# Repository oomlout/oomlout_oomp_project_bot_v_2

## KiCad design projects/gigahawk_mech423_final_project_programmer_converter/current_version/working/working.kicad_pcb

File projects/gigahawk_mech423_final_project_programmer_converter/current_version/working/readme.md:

# mech423_final_project
 
## summary 
* id: gigahawk_mech423_final_project_programmer_converter
* user: gigahawk
* name: mech423_final_project
* board: programmer_converter
* repo: https://github.com/Gigahawk/mech423_final_project
* src_file_repo_kicad_pcb: pcb/logic_handle.kicad_pcb
* src_file_repo_kicad_pcb_link: https://github.com/Gigahawk/mech423_final_project/tree/master/pcb/logic_handle.kicad_pcb
* src_file_repo_kicad_sch: pcb/conn_common.kicad_sch
* src_file_repo_kicad_sch_link: https://github.com/Gigahawk/mech423_final_project/tree/master/pcb/conn_common.kicad_sch

* src_file_repo_sch: 
* src_file_repo_sch_link: https://github.com/Gigahawk/mech423_final_project/tree/master/
* full details link: https://github.com/oomlout/oomlout_oomp_project_bot_v_2/tree/main/projects/gigahawk_mech423_final_project_programmer_converter/current_version/working

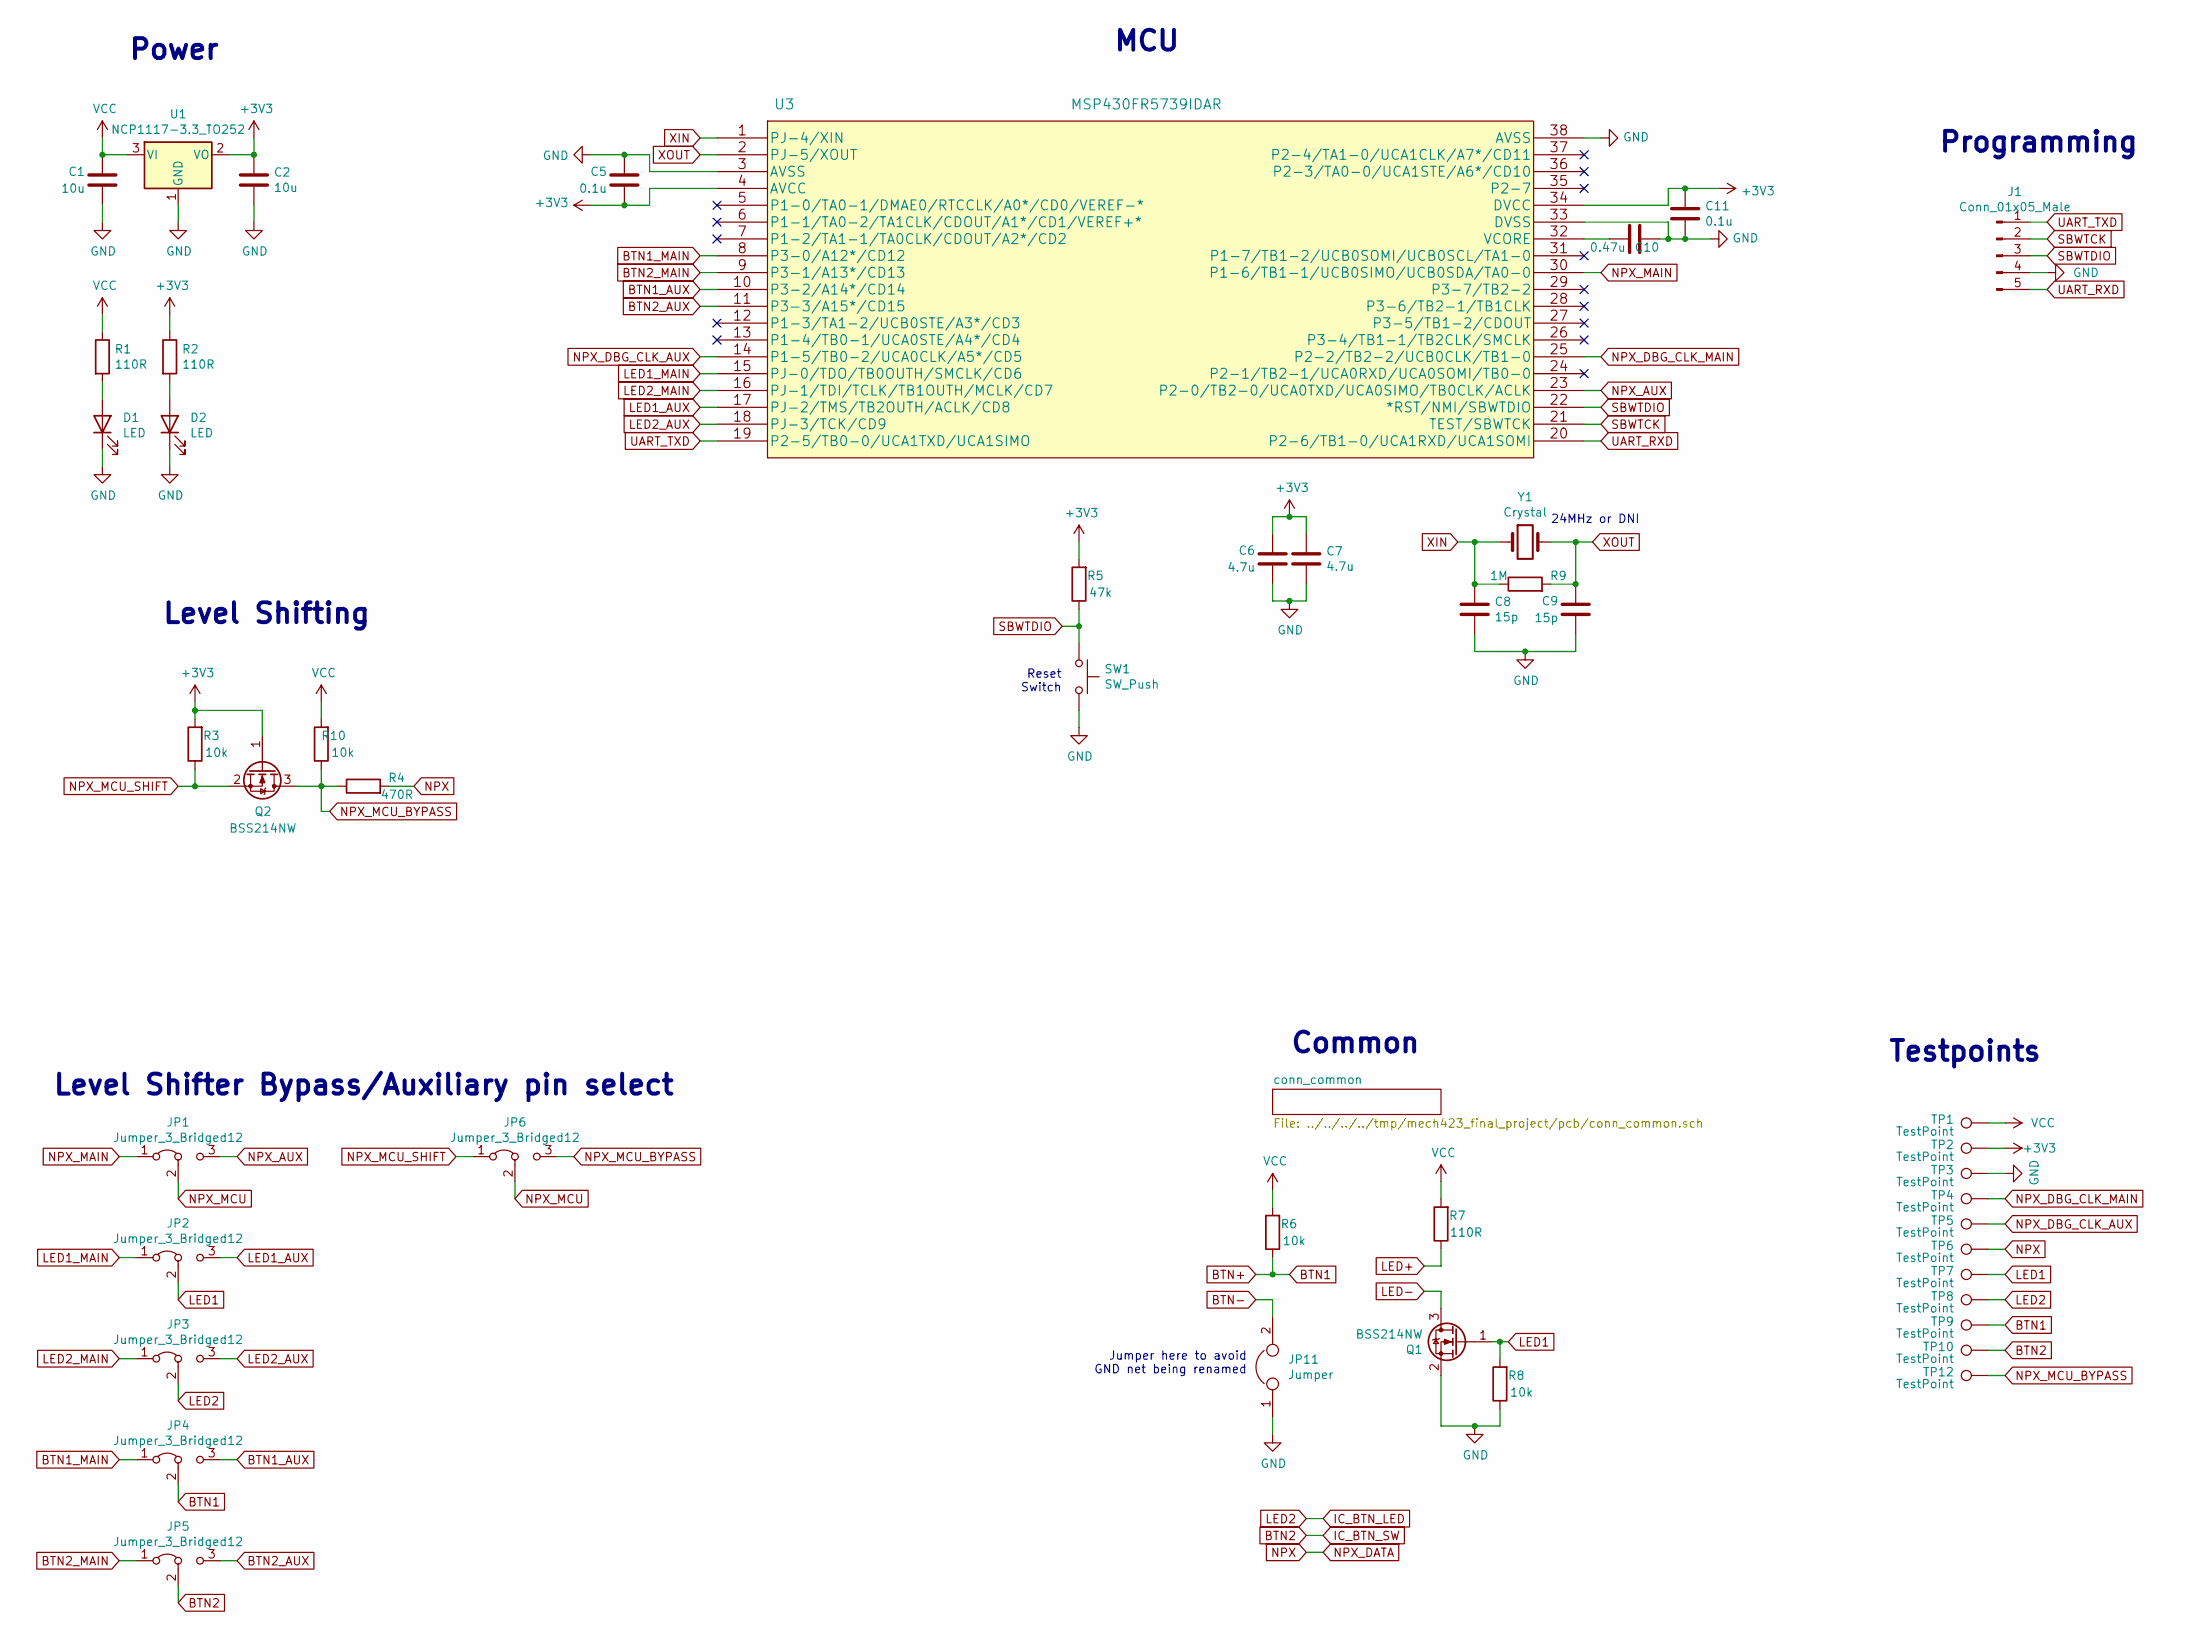
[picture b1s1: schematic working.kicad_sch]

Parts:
C1, C2: 10u; C_0805_2012Metric; Digikey 1276-6456-1-ND
C5, C11: 0.1u; C_0805_2012Metric; Digikey 478-10836-1-ND
C6, C7: 4.7u; C_0805_2012Metric; Digikey 1276-1259-1-ND
C8, C9: 15p; C_0805_2012Metric; Digikey 478-1306-1-ND
C10: 0.47u; C_0805_2012Metric; Digikey 478-10438-1-ND
D1, D2: LED; LED_0603_1608Metric; Digikey 160-1832-1-ND
J1: Conn_01x05_Male; PinHeader_1x05_P2.54mm_Vertical
JP1, JP2, JP3, JP4, JP5, JP6: Jumper_3_Bridged12; SolderJumper-3_P1.3mm_Bridged2Bar12_Pad1.0x1.5mm
JP11: Jumper; SolderJumper-2_P1.3mm_Bridged2Bar_Pad1.0x1.5mm
Q1, Q2: BSS214NW; SOT-323_SC-70; Digikey BSS214NWH6327XTSA1CT-ND
R1, R2, R7: 110R; R_0805_2012Metric; Digikey RMCF0805JT110RCT-ND
R3, R6, R8, R10: 10k; R_0805_2012Metric; Digikey RMCF0805JT10K0CT-ND
R4: 470R; R_0805_2012Metric; Digikey A129745CT-ND
R5: 47k; R_0805_2012Metric; Digikey A130144CT-ND
R9: 1M; R_0805_2012Metric; Digikey A106058CT-ND
SW1: SW_Push; SW_SPST_TL3342; Digikey EG5470CT-ND
TP1, TP2, TP3, TP4, TP5, TP6, TP7, TP8, TP9, TP10, TP12: TestPoint; TestPoint_Pad_2.0x2.0mm
U1: NCP1117-3.3_TO252; TO-252-2; Digikey NCP1117ST33T3GOSCT-ND
U3: MSP430FR5739IDAR; Digikey 296-29235-1-ND
Y1: Crystal; Crystal_SMD_AWSZT-CV-2Pin_3.7x3.1mm; Digikey 535-10028-2-ND

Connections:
+3V3: C2.1, C5.1, C6.2, C7.1, C11.1, Q2.1 (G), R2.1, R3.2, R5.2, TP2.1, U1.2 (VO), U3.4 (AVCC), U3.34 (DVCC)
BTN1_AUX: JP4.3 (B), U3.10 (P3-2/A14*/CD14)
BTN1_MAIN: JP4.1 (A), U3.8 (P3-0/A12*/CD12)
BTN2: JP5.2 (C), TP10.1; also elsewhere on the board
BTN2_AUX: JP5.3 (B), U3.11 (P3-3/A15*/CD15)
BTN2_MAIN: JP5.1 (A), U3.9 (P3-1/A13*/CD13)
BTN+: JP4.2 (C), R6.1, TP9.1; also elsewhere on the board
BTN-: JP11.2; also elsewhere on the board
GND: C1.1, C2.2, C5.2, C6.1, C7.2, C8.2, C9.1, C10.2, C11.2, D1.1 (K), D2.1 (K), J1.4, JP11.1, Q1.2 (S), R8.1, SW1.2, TP3.1, U1.1 (GND), U3.3 (AVSS), U3.33 (DVSS), U3.38 (AVSS); also elsewhere on the board
IC_BTN_LED: JP3.2 (C), TP8.1; also elsewhere on the board
LED1: JP2.2 (C), Q1.1 (G), R8.2, TP7.1
LED1_AUX: JP2.3 (B), U3.17 (PJ-2/TMS/TB2OUTH/ACLK/CD8)
LED1_MAIN: JP2.1 (A), U3.15 (PJ-0/TDO/TB0OUTH/SMCLK/CD6)
LED2_AUX: JP3.3 (B), U3.18 (PJ-3/TCK/CD9)
LED2_MAIN: JP3.1 (A), U3.16 (PJ-1/TDI/TCLK/TB1OUTH/MCLK/CD7)
LED+: R7.1; also elsewhere on the board
LED-: Q1.3 (D); also elsewhere on the board
NPX: R4.2, TP6.1; also elsewhere on the board
NPX_AUX: JP1.3 (B), U3.23 (P2-0/TB2-0/UCA0TXD/UCA0SIMO/TB0CLK/ACLK)
NPX_DBG_CLK_AUX: TP5.1, U3.14 (P1-5/TB0-2/UCA0CLK/A5*/CD5)
NPX_DBG_CLK_MAIN: TP4.1, U3.25 (P2-2/TB2-2/UCB0CLK/TB1-0)
NPX_MAIN: JP1.1 (A), U3.30 (P1-6/TB1-1/UCB0SIMO/UCB0SDA/TA0-0)
NPX_MCU: JP1.2 (C), JP6.2 (C)
NPX_MCU_BYPASS: JP6.3 (B), Q2.3 (D), R4.1, R10.1, TP12.1
NPX_MCU_SHIFT: JP6.1 (A), Q2.2 (S), R3.1
unnamed: C10.1, U3.32 (VCORE)
unnamed: D1.2 (A), R1.2
unnamed: D2.2 (A), R2.2
SBWTCK: J1.2, U3.21 (TEST/SBWTCK)
SBWTDIO: J1.3, R5.1, SW1.1, U3.22 (*RST/NMI/SBWTDIO)
UART_RXD: J1.5, U3.20 (P2-6/TB1-0/UCA1RXD/UCA1SOMI)
UART_TXD: J1.1, U3.19 (P2-5/TB0-0/UCA1TXD/UCA1SIMO)
VCC: C1.2, R1.1, R6.2, R7.2, R10.2, TP1.1, U1.3 (VI); also elsewhere on the board
XIN: C8.1, R9.1, U3.1 (PJ-4/XIN), Y1.1
XOUT: C9.2, R9.2, U3.2 (PJ-5/XOUT), Y1.2

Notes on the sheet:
Programming
Level Shifting
Level Shifter Bypass/Auxiliary pin select
Jumper here to avoid GND net being renamed
Testpoints
Reset Switch
24MHz or DNI
Power
Common
MCU

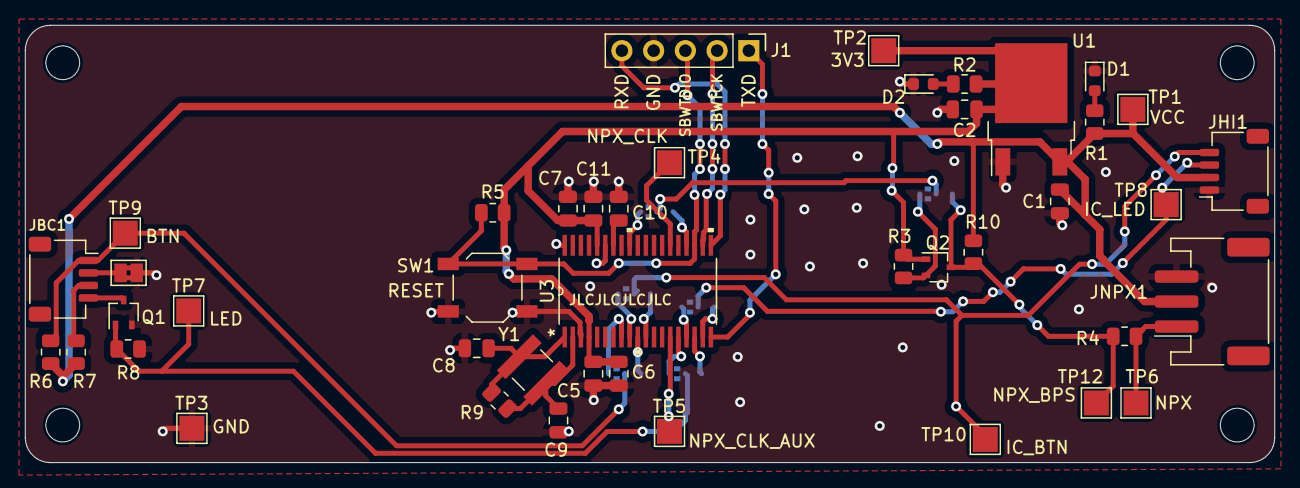
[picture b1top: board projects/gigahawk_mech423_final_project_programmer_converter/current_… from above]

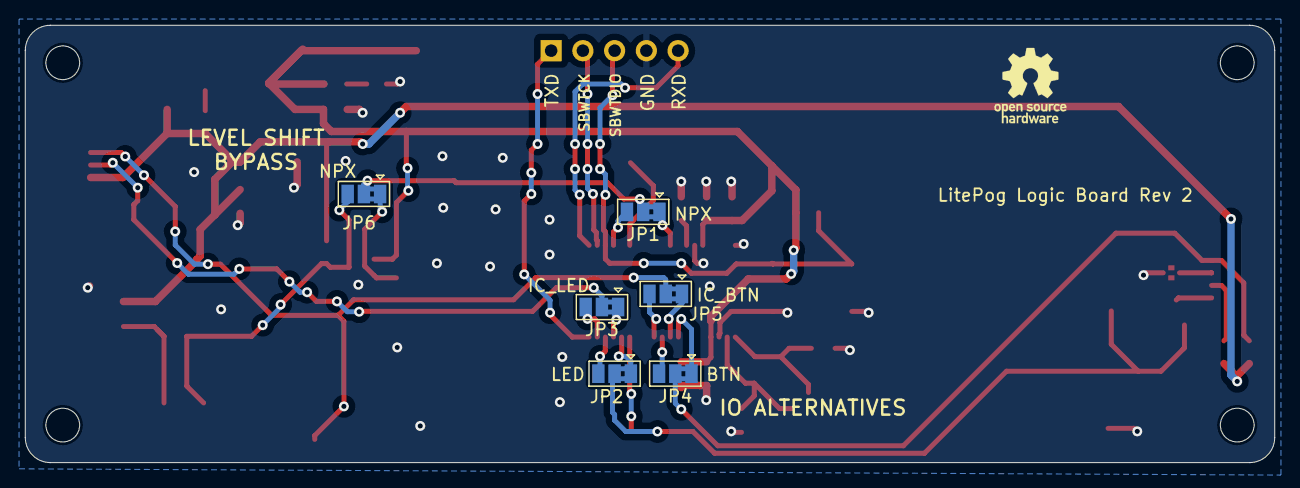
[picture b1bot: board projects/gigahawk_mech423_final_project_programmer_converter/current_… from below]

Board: 2 copper layers, 100.0 x 35.0 mm, 54 parts (7 on the bottom side), 35 nets.

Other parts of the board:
H1, H2, H3, H4: MountingHole; MountingHole_2.7mm_M2.5
JBC1: Conn_01x04; JST_SH_SM04B-SRSS-TB_1x04-1MP_P1.00mm_Horizontal
JHI1: Conn_01x04; JST_SH_SM04B-SRSS-TB_1x04-1MP_P1.00mm_Horizontal
JNPX1: Conn_01x03; JST_PH_S3B-PH-SM4-TB_1x03-1MP_P2.00mm_Horizontal
LOGO1: Logo_Open_Hardware_Small; OSHW-Logo_5.7x6mm_SilkScreen

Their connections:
BTN2: JHI1.4; also elsewhere on the board
BTN+: JBC1.1; also elsewhere on the board
BTN-: JBC1.2; also elsewhere on the board
GND: JHI1.1, JNPX1.3; also elsewhere on the board
IC_BTN_LED: JHI1.3; also elsewhere on the board
LED+: JBC1.3; also elsewhere on the board
LED-: JBC1.4; also elsewhere on the board
NPX: JNPX1.1; also elsewhere on the board
VCC: JHI1.2, JNPX1.2; also elsewhere on the board

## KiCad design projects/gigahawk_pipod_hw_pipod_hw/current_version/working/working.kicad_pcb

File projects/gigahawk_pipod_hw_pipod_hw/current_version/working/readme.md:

# pipod_hw
 
## summary 
* id: gigahawk_pipod_hw_pipod_hw
* user: gigahawk
* name: pipod_hw
* board: pipod_hw
* repo: https://github.com/Gigahawk/pipod_hw
* src_file_repo_kicad_pcb: pipod_compute.kicad_pcb
* src_file_repo_kicad_pcb_link: https://github.com/Gigahawk/pipod_hw/tree/master/pipod_compute.kicad_pcb
* src_file_repo_kicad_sch: audio.kicad_sch
* src_file_repo_kicad_sch_link: https://github.com/Gigahawk/pipod_hw/tree/master/audio.kicad_sch

* src_file_repo_sch: 
* src_file_repo_sch_link: https://github.com/Gigahawk/pipod_hw/tree/master/
* full details link: https://github.com/oomlout/oomlout_oomp_project_bot_v_2/tree/main/projects/gigahawk_pipod_hw_pipod_hw/current_version/working

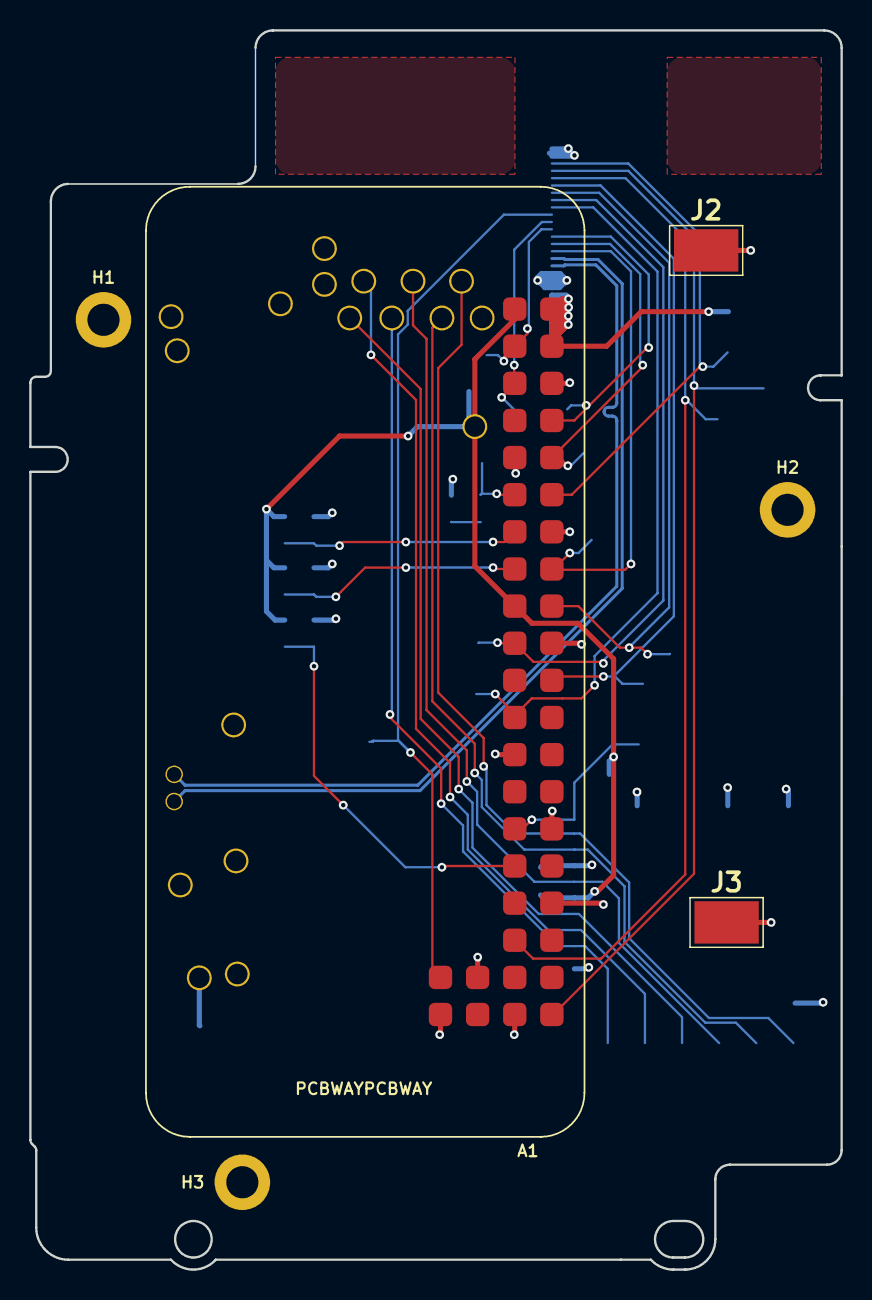
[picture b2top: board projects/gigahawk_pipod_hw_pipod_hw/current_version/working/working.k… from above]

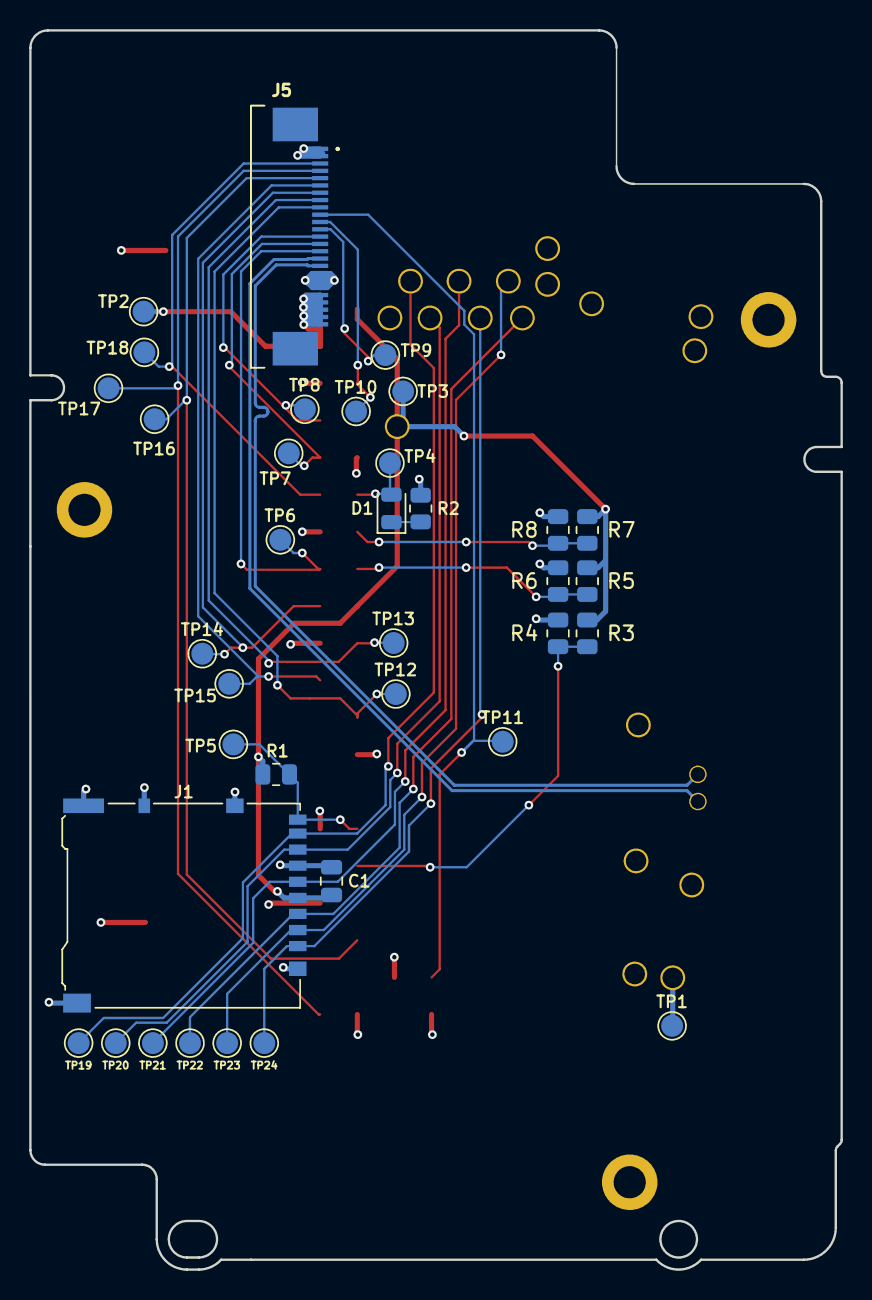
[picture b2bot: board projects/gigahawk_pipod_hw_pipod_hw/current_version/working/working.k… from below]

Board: 4 copper layers, 55.5 x 84.8 mm, 43 parts (36 on the bottom side), 30 nets.

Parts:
A1: RASPBERRY_PI_ZERO_SMT; RASPI_ZERO_1_3_SMT_LOW_PROFILE
C1: 10u; C_0805_2012Metric
D1: GRN; LED_0805_2012Metric
H1, H2, H3: MountingHole_Pad; MountingHole_2.2mm_M2_DIN965_Pad
J1: Micro_SD_Card; microSD_HC_Hirose_DM3AT-SF-PEJM5
J2, J3: S7041-42R
J5: 2-1734839-5; 217348395
LOGO1: Logo_Open_Hardware_Large; OSHW-Logo2_9.8x8mm_Mask
R1, R4, R6, R8: 10k; R_0805_2012Metric
R2: 470R; R_0805_2012Metric
R3, R5, R7: DNI; R_0805_2012Metric
TP1, TP2, TP3, TP4, TP5, TP6, TP7, TP8, TP9, TP10, TP11, TP12, TP13, TP14, TP15, TP16, TP17, TP18, TP19, TP20, TP21, TP22, TP23, TP24: TestPoint; TestPoint_Pad_D1.5mm

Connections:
+3V3: A1.1 (3V3), A1.17 (3V3), A1.PP8 (3V3), C1.2, J1.4 (VDD), R1.2, R3.1, R5.1, R7.1, TP3.1
GND: A1.6 (GND), A1.9 (GND), A1.14 (GND), A1.20 (GND), A1.25 (GND), A1.30 (GND), A1.34 (GND), A1.39 (GND), A1.PP5 (GND), A1.PP6 (GND), A1.PP35 (GND), A1.RUN1 (GND), A1.TV2 (GND), C1.1, H1.1, H2.1, H3.1, J1.6 (VSS), J1.10 (DET_A), J1.11 (SHIELD), J2.1, J3.1, J5.1, J5.2, J5.18, J5.19, J5.20, R2.1, R4.2, R6.2, R8.2, TP1.1
HP_SL_VIDEO: A1.TV1 (TV), J5.10, TP11.1
HWID0: A1.31 (GPIO6), R3.2, R4.1
HWID1: A1.15 (GPIO22), R5.2, R6.1
HWID2: A1.13 (GPIO27), R7.2, R8.1
unnamed: A1.11 (GPIO17), D1.2 (A), TP4.1
unnamed: D1.1 (K), R2.2
PI_DISP_DC: A1.18 (GPIO24), J5.7, TP14.1
PI_DISP_MOSI: A1.19 (GPIO10/MOSI), J5.8, TP13.1
PI_DISP_RST: A1.22 (GPIO25), J5.6, TP15.1
PI_DISP_SCK: A1.23 (GPIO11/SCLK), J5.9, TP12.1
PI_I2S_BCK: A1.12 (GPIO18/PCM_CLK), J5.3, TP18.1
PI_I2S_DIN: A1.40 (GPIO21/PCM_DOUT), J5.4, TP17.1
PI_I2S_LRCK: A1.35 (GPIO19/PCM_FS), J5.5, TP16.1
PI_USB_MUXED_D+: A1.PP22 (USB_D+), J5.16
PI_USB_MUXED_D-: A1.PP23 (USB_D-), J5.17
SD_CD: A1.PP19 (SD_CD), J1.2 (DAT3/CD), TP23.1
SD_CLK: A1.PP14 (SD_CLK), J1.5 (CLK), TP21.1
SD_CMD: A1.PP15 (SD_CMD), J1.3 (CMD), TP22.1
SD_DAT0: A1.PP16 (SD_DAT0), J1.7 (DAT0), TP20.1
SD_DAT1: A1.PP17 (SD_DAT1), J1.8 (DAT1), TP19.1
SD_DAT2: A1.PP18 (SD_DAT2), J1.1 (DAT2), TP24.1
SD_DET: A1.29 (GPIO5), J1.9 (DET_B), R1.1, TP5.1
SMC_INT: A1.16 (GPIO23), J5.15, TP6.1
SMC_PI_I2C_SCL: A1.5 (GPIO3/SCL), J5.11, TP10.1
SMC_PI_I2C_SDA: A1.3 (GPIO2/SDA), J5.12, TP9.1
SMC_RX_PI_TX: A1.8 (GPIO14/TXD), J5.13, TP8.1
SMC_TX_PI_RX: A1.10 (GPIO15/RXD), J5.14, TP7.1
VCC: A1.2 (5V), A1.4 (5V), J5.21, J5.22, J5.23, J5.24, J5.25, TP2.1

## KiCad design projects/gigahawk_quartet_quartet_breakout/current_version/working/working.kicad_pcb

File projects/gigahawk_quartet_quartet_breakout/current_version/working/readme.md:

# quartet
 
## summary 
* id: gigahawk_quartet_quartet_breakout
* user: gigahawk
* name: quartet
* board: quartet_breakout
* repo: https://github.com/Gigahawk/quartet
* src_file_repo_kicad_pcb: quartet_breakout.kicad_pcb
* src_file_repo_kicad_pcb_link: https://github.com/Gigahawk/quartet/tree/master/quartet_breakout.kicad_pcb

* src_file_repo_sch: 
* src_file_repo_sch_link: https://github.com/Gigahawk/quartet/tree/master/
* full details link: https://github.com/oomlout/oomlout_oomp_project_bot_v_2/tree/main/projects/gigahawk_quartet_quartet_breakout/current_version/working

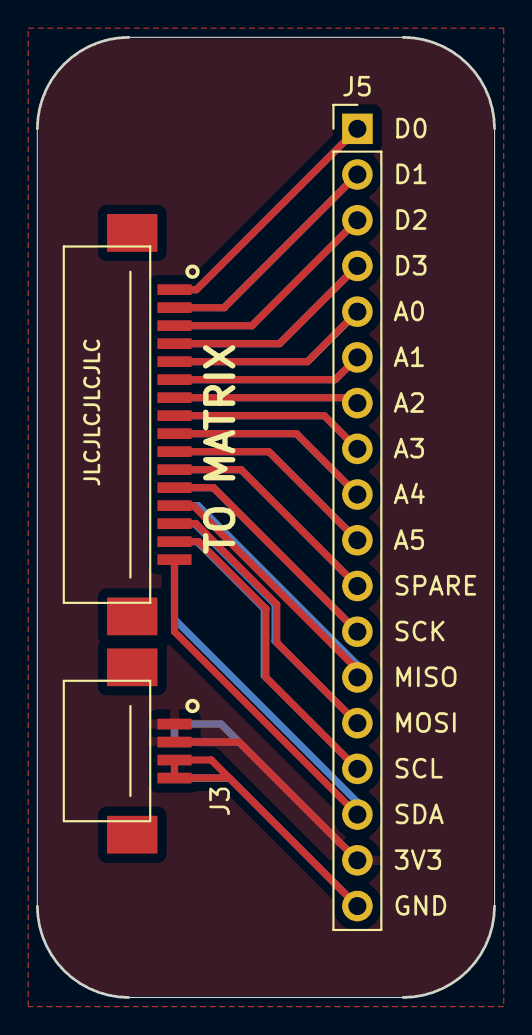
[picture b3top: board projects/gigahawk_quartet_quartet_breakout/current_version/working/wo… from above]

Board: 2 copper layers, 25.4 x 53.3 mm, 3 parts (1 on the bottom side), 18 nets.

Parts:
J2: QUARTET_RECV; QUARTET_RECV_MATRIX
J3: QUARTET_RECV; QUARTET_RECV_MAIN
J5: Conn_01x18; PinHeader_1x18_P2.54mm_Vertical

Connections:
+3V3: J2.17, J2.18, J3.17, J3.18, J5.17
A0: J2.5, J3.5, J5.5
A1: J2.6, J3.6, J5.6
A2: J2.7, J3.7, J5.7
A3: J2.8, J3.8, J5.8
A4: J2.9, J3.9, J5.9
A5: J2.10, J3.10, J5.10
D0: J2.1, J3.1, J5.1
D1: J2.2, J3.2, J5.2
D2: J2.3, J3.3, J5.3
D3: J2.4, J3.4, J5.4
GND: J2.19, J2.20, J3.19, J3.20, J5.18
MISO: J2.13, J3.13, J5.13
MOSI: J2.14, J3.14, J5.14
SCK: J2.12, J3.12, J5.12
SCL: J2.15, J3.15, J5.15
SDA: J2.16, J3.16, J5.16
SPARE: J2.11, J3.11, J5.11

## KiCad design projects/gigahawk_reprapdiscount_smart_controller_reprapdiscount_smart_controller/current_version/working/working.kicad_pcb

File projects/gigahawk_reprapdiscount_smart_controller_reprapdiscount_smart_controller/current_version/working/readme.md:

# reprapdiscount_smart_controller
 
## summary 
* id: gigahawk_reprapdiscount_smart_controller_reprapdiscount_smart_controller
* user: gigahawk
* name: reprapdiscount_smart_controller
* board: reprapdiscount_smart_controller
* repo: https://github.com/Gigahawk/reprapdiscount_smart_controller
* src_file_repo_kicad_pcb: reprapdiscount_smart_controller.kicad_pcb
* src_file_repo_kicad_pcb_link: https://github.com/Gigahawk/reprapdiscount_smart_controller/tree/master/reprapdiscount_smart_controller.kicad_pcb
* src_file_repo_kicad_sch: reprapdiscount_smart_controller.kicad_sch
* src_file_repo_kicad_sch_link: https://github.com/Gigahawk/reprapdiscount_smart_controller/tree/master/reprapdiscount_smart_controller.kicad_sch

* src_file_repo_sch: 
* src_file_repo_sch_link: https://github.com/Gigahawk/reprapdiscount_smart_controller/tree/master/
* full details link: https://github.com/oomlout/oomlout_oomp_project_bot_v_2/tree/main/projects/gigahawk_reprapdiscount_smart_controller_reprapdiscount_smart_controller/current_version/working

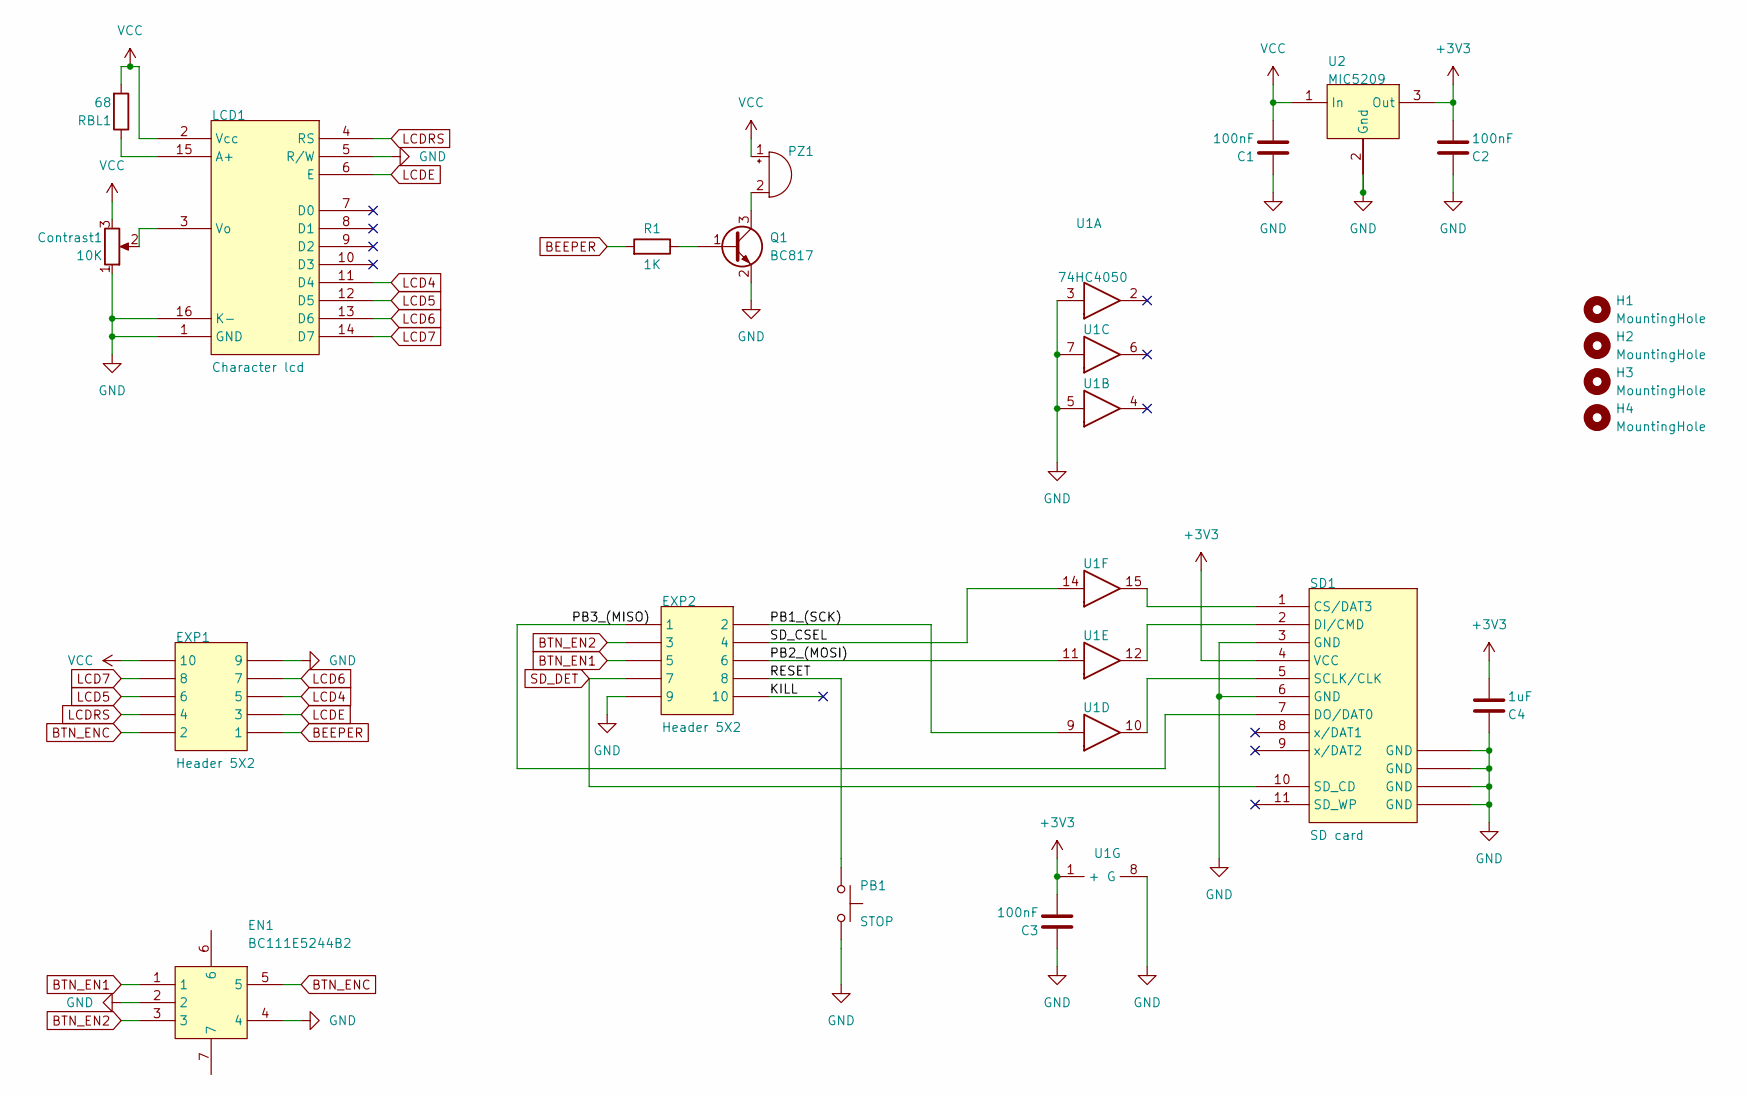
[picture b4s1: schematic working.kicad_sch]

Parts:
C1, C2, C3: 100nF; C_0805_2012Metric_Pad1.18x1.45mm_HandSolder
C4: 1uF; C_1206_3216Metric_Pad1.33x1.80mm_HandSolder
Contrast1: 10K; RES TRIMPOT
EN1: BC111E5244B2; ROTARY ENCODER
EXP1, EXP2: Header 5X2; HDR2X5_EXP
H1, H2, H3, H4: MountingHole; MountingHole_3mm
LCD1: Character lcd; HDR1X16
PB1: STOP; SW_PUSH_6mm_H5mm
PZ1: PIEZO; PIEZO 11MM
Q1: BC817; SOT-23
R1: 1K; R_0805_2012Metric_Pad1.20x1.40mm_HandSolder
RBL1: 68; R_1206_3216Metric_Pad1.30x1.75mm_HandSolder
SD1: SD card; SD_card socket
U1: 74HC4050; SO-16_3.9x9.9mm_P1.27mm
U2: MIC5209; SOT-223

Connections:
+3V3: C2.2, C3.2, C4.2, SD1.4 (VCC), U1.1 (+), U2.3 (Out)
/KILL: EXP2.10
/PB1_(SCK): EXP2.2, U1.9
/PB2_(MOSI): EXP2.6, U1.11
/PB3_(MISO): EXP2.1, SD1.7 (DO/DAT0)
/RESET: EXP2.8, PB1.1
/SD_CSEL: EXP2.4, U1.14
BEEPER: EXP1.1, R1.2
BTN_EN1: EN1.1, EXP2.5
BTN_EN2: EN1.3, EXP2.3
BTN_ENC: EN1.5, EXP1.2
GND: C1.1, C2.1, C3.1, C4.1, Contrast1.1, EN1.2, EN1.4, EXP1.9, EXP2.9, LCD1.1 (GND), LCD1.5 (R/W), LCD1.16 (K-), PB1.2, Q1.2 (E), SD1.3 (GND), SD1.6 (GND), SD1.12 (GND), U1.3, U1.5, U1.7, U1.8 (G), U2.2 (Gnd), U2.4 (Gnd)
LCD4: EXP1.5, LCD1.11 (D4)
LCD5: EXP1.6, LCD1.12 (D5)
LCD6: EXP1.7, LCD1.13 (D6)
LCD7: EXP1.8, LCD1.14 (D7)
LCDE: EXP1.3, LCD1.6 (E)
LCDRS: EXP1.4, LCD1.4 (RS)
unnamed: LCD1.15 (A+), RBL1.1
unnamed: Contrast1.2, LCD1.3 (Vo)
unnamed: PZ1.2 (+), Q1.3 (C)
unnamed: Q1.1 (B), R1.1
unnamed: SD1.1 (CS/DAT3), U1.15
unnamed: SD1.2 (DI/CMD), U1.12
unnamed: SD1.5 (SCLK/CLK), U1.10
SD_DET: EXP2.7, SD1.10 (SD_CD)
VCC: C1.2, Contrast1.3, EXP1.10, LCD1.2 (Vcc), PZ1.1 (-), RBL1.2, U2.1 (In)

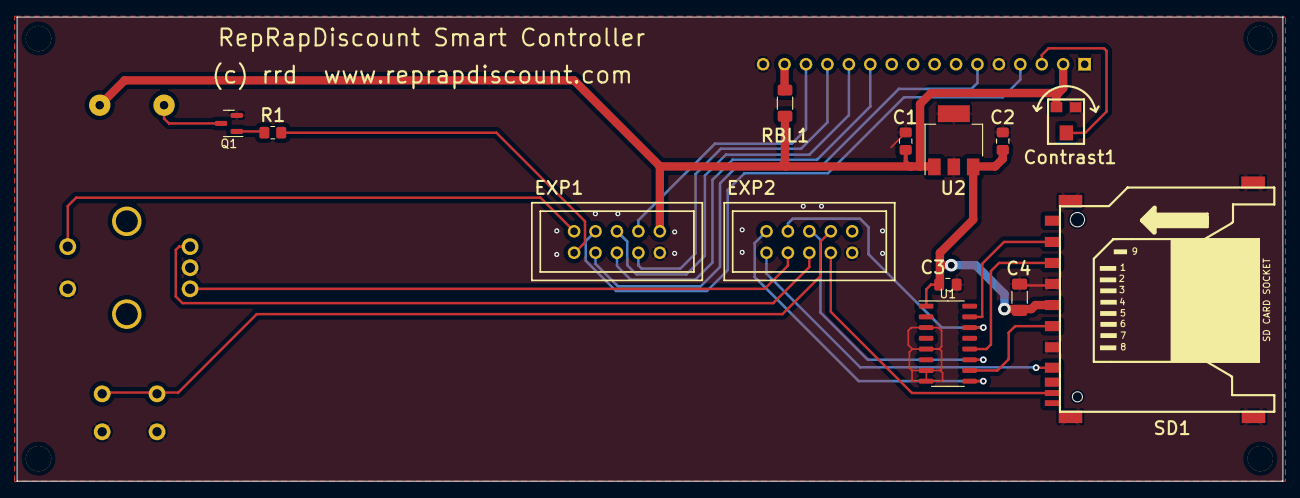
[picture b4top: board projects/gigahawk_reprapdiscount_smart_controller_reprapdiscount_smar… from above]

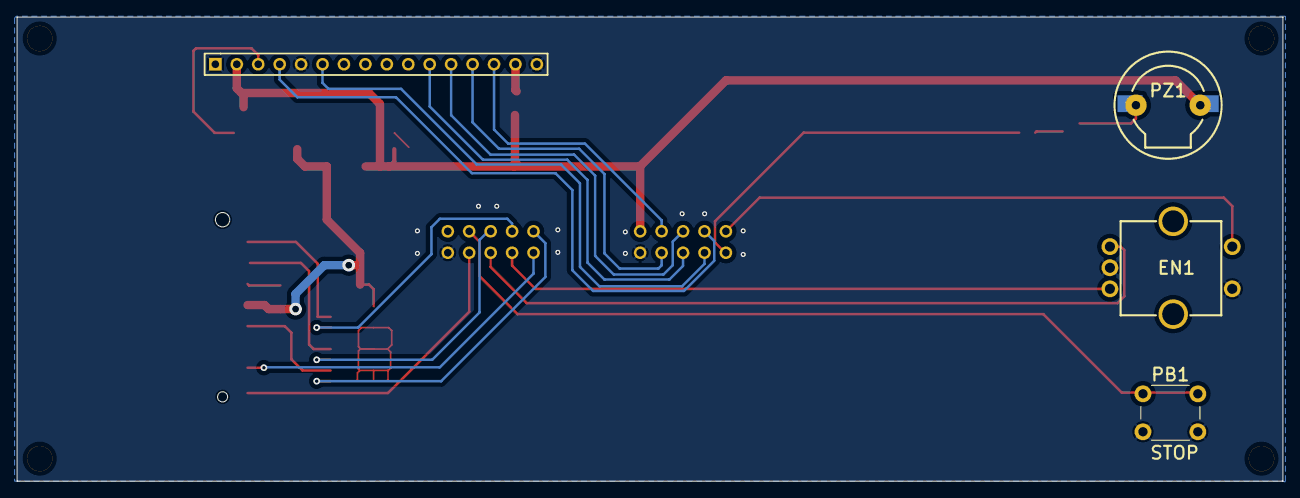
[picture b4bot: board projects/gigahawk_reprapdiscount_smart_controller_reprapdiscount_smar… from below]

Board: 2 copper layers, 150.0 x 55.0 mm, 21 parts (4 on the bottom side), 26 nets.
